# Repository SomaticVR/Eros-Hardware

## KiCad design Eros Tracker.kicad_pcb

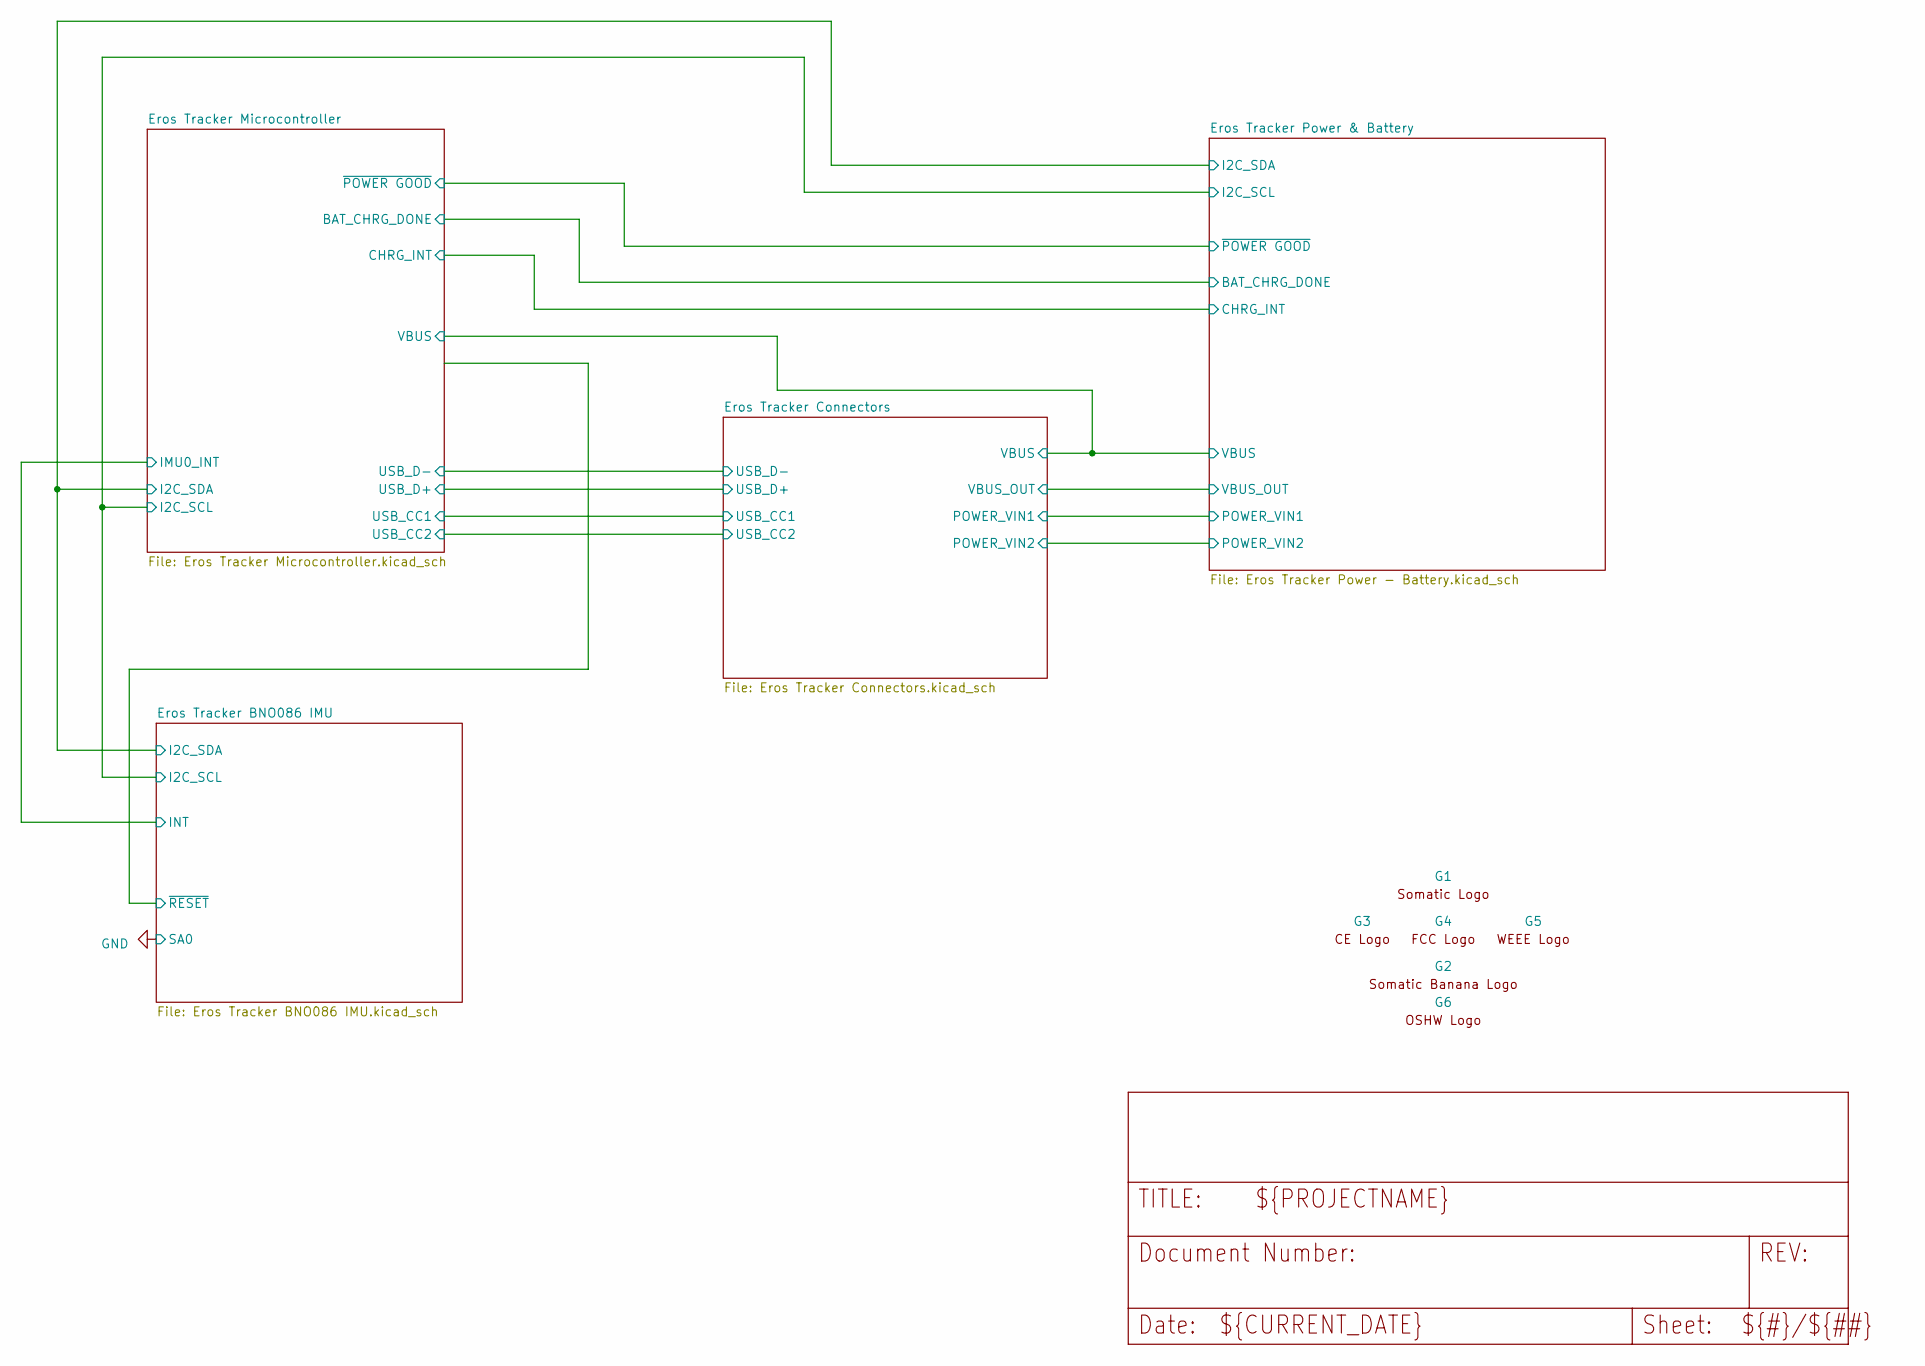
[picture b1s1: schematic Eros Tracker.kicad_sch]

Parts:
G1: SomaticLogo
G2: SomaticBananaLogo
G3: CE-Logo_7.0x5.0mm_SilkScreen
G4: FCC-Logo_6.2x5.0mm_SilkScreen
G5: WEEE-Logo_4.2x6mm_SilkScreen
G6: OSHW-Logo2_7.3x6mm_SilkScreen

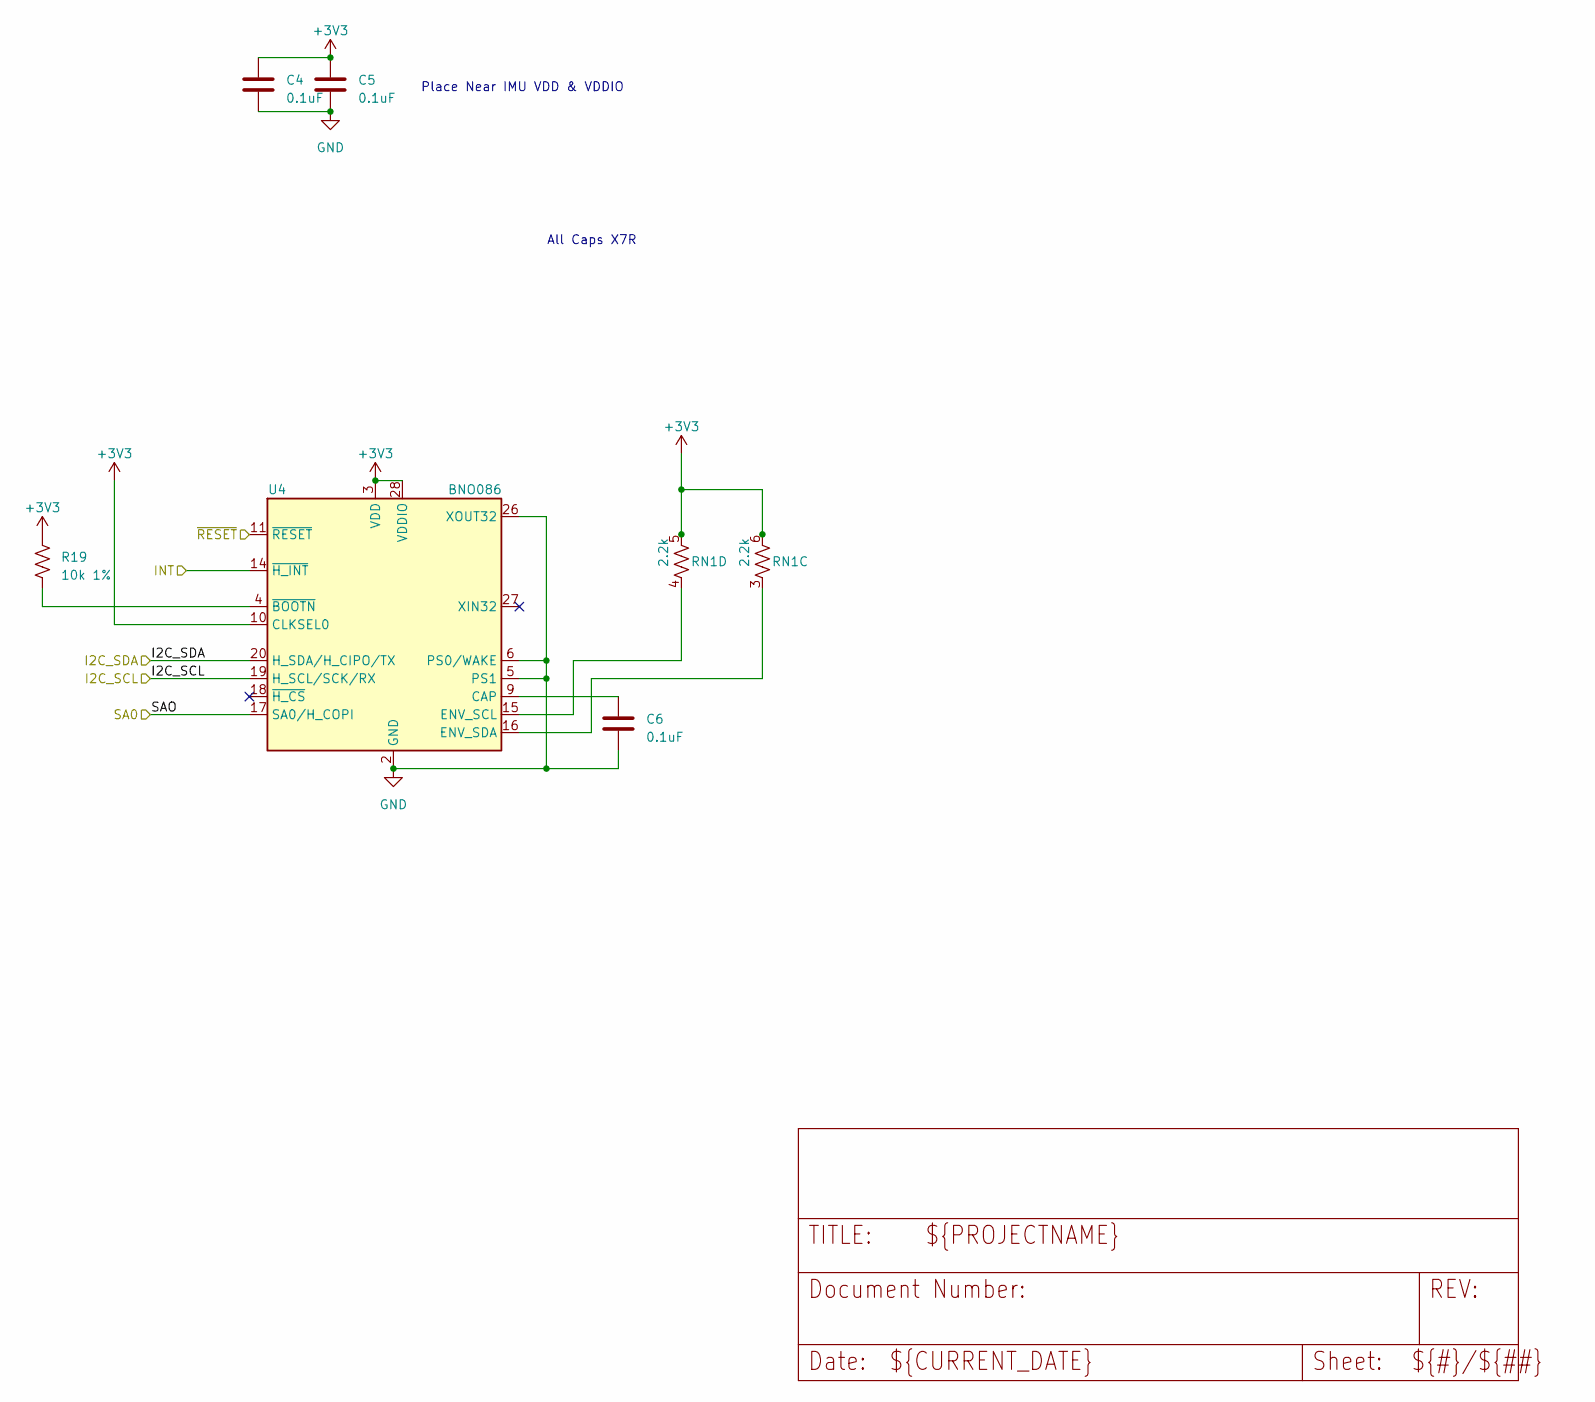
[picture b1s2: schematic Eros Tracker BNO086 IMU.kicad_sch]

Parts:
C4, C5, C6: 0.1uF; C_0402_1005Metric; Manufacturer_Part_Number CL05B104KA5NNNC; Mouser Part Number 187-CL05B104KA5NNNC
R19: 10k 1%; R_0402_1005Metric; Manufacturer_Part_Number RT0402FRE0710KL; Mouser Part Number 603-RT0402FRE0710KL
RN1: 2.2k; CAY10-xxxJ4; Manufacturer_Part_Number CAY10-222J4LF; Mouser Part Number 652-CAY10-222J4LF
U4: BNO086; LGA-28_5.2x3.8mm_P0.5mm; Manufacturer_Part_Number BNO086; DigiKey Part Number 1888-BNO086CT-ND

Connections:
+3V3: C4.1, C5.1, R19.1, RN1.5, RN1.6, U4.3 (VDD), U4.10 (CLKSEL0), U4.28 (VDDIO); also elsewhere on the board
/Eros Tracker BNO086 IMU/I2C_SCL: U4.19 (H_SCL/SCK/RX); also elsewhere on the board
/Eros Tracker BNO086 IMU/I2C_SDA: U4.20 (H_SDA/H_CIPO/TX); also elsewhere on the board
/Eros Tracker BNO086 IMU/INT: U4.14 (~H_INT); also elsewhere on the board
/Eros Tracker BNO086 IMU/~RESET: U4.11 (~RESET)
GND: C4.2, C5.2, C6.2, U4.2 (GND), U4.5 (PS1), U4.6 (PS0/WAKE), U4.17 (SA0/H_COPI), U4.25 (GNDIO), U4.26 (XOUT32); also elsewhere on the board
unnamed: C6.1, U4.9 (CAP)
unnamed: RN1.4, U4.15 (ENV_SCL)
unnamed: RN1.3, U4.16 (ENV_SDA)
unnamed: R19.2, U4.4 (~BOOTN)

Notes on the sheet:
Place Near IMU VDD & VDDIO
All Caps X7R

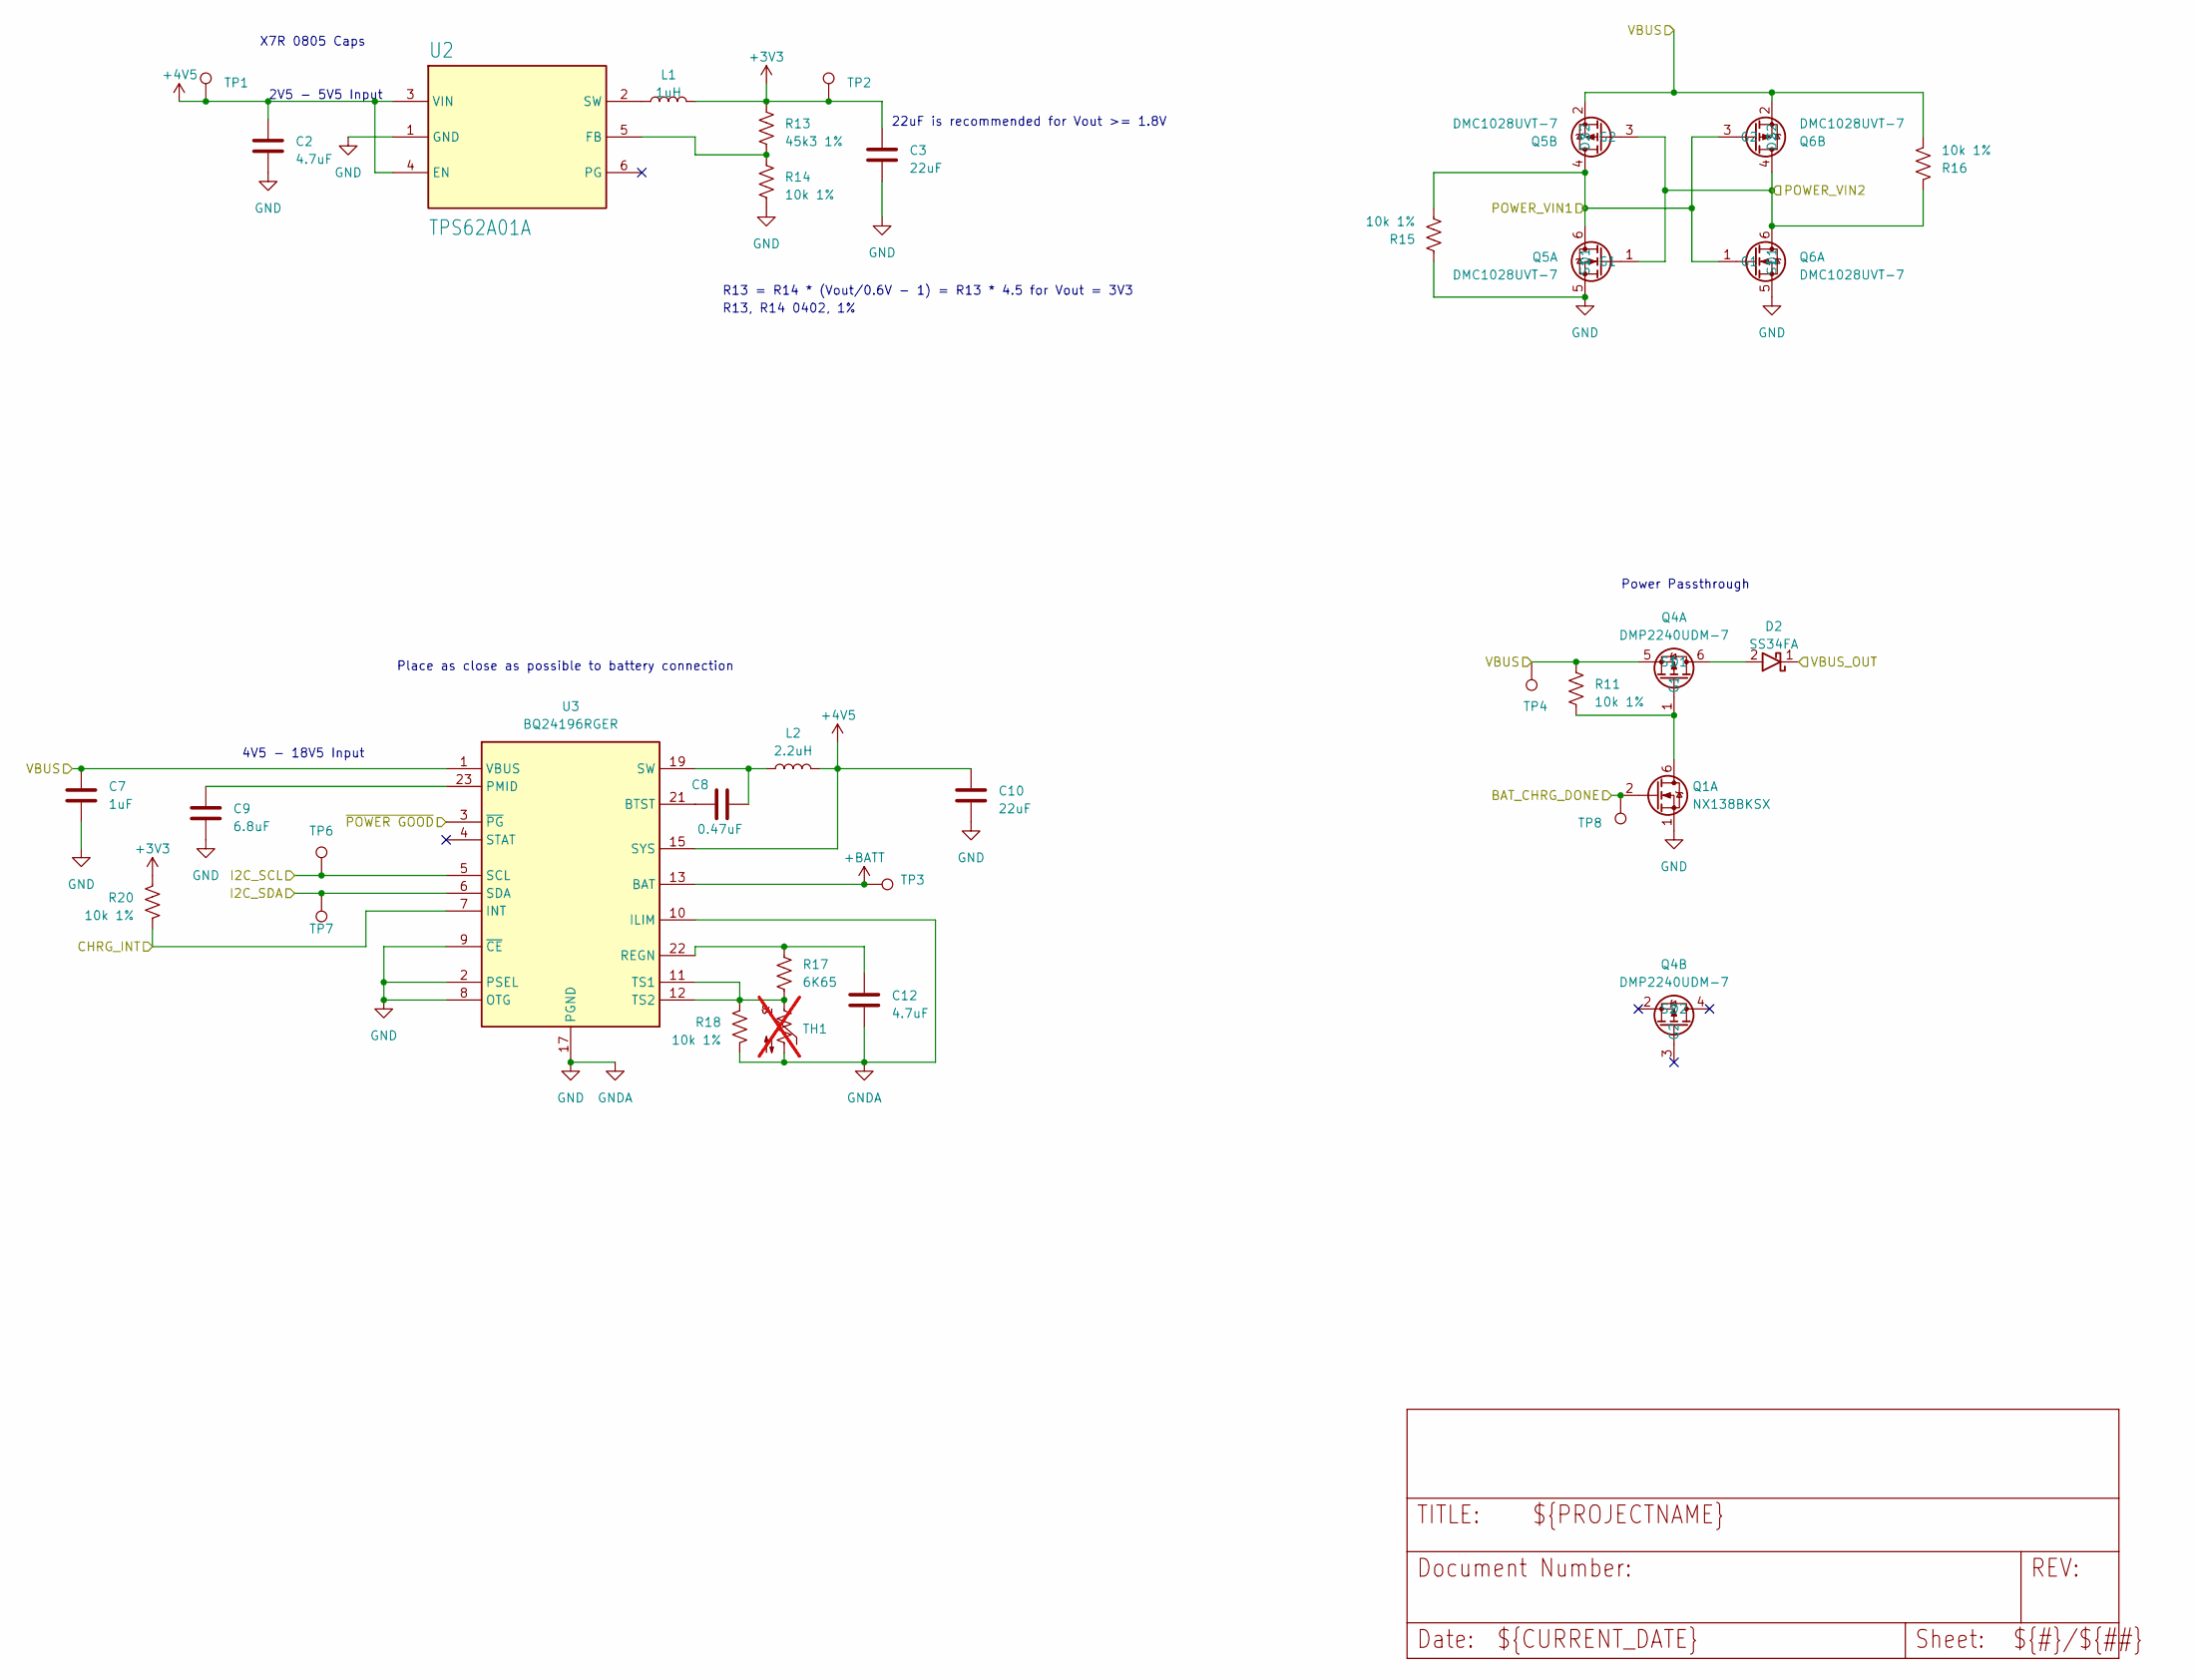
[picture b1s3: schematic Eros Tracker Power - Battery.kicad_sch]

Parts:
C2, C12: 4.7uF; C_0603_1608Metric; Manufacturer_Part_Number GRM188Z71C475KE21D; Mouser Part Number 81-GRM188Z71C475KE1D
C3, C10: 22uF; C_0805_2012Metric; Manufacturer_Part_Number GRM21BZ71A226ME15L; Mouser Part Number 81-GRM21BZ71A226ME5L
C7: 1uF; C_0603_1608Metric; Manufacturer_Part_Number MLASU168AB7105KTNA01; Mouser Part Number 963-MLASU168AB7105KT
C8: 0.47uF; C_0402_1005Metric; Manufacturer_Part_Number CC0402KRX7R6BB474; Mouser Part Number 603-CC0402KR6BB474
C9: 6.8uF; C_1210_3225Metric; Manufacturer_Part_Number C3225X7R1E685K250AB; Mouser Part Number 810-C3225X7R1E685K11
D2: SS34FA; SODFL3618X143N; Mouser Part Number 512-SS34FA
L1: 1uH; DFE2HCAH1R0MJ0L; Manufacturer_Part_Number DFE252012F-1R0M=P2; Mouser Part Number 81-DFE252012F-1R0MP2
L2: 2.2uH; 1277ASH100MP2; Manufacturer_Part_Number DFE322512F-2R2M=P2; Mouser Part Number 81-DFE322512F-2R2MP2
Q1: NX138BKSX; SOT65P210X110-6N; Mouser Part Number 771-NX138BKSX
Q4: DMP2240UDM-7; SOT95P285X140-6N; Mouser Part Number 621-DMP2240UDM-7
Q5, Q6: DMC1028UVT-7; SOT95P285X140-6N; Mouser Part Number 621-DMC1028UVT-7
R11, R14, R15, R16, R18, R20: 10k 1%; R_0402_1005Metric; Manufacturer_Part_Number RT0402FRE0710KL; Mouser Part Number 603-RT0402FRE0710KL
R13: 45k3 1%; R_0402_1005Metric; Manufacturer_Part_Number RR0510P-4532-D; Mouser Part Number 754-RR0510P-4532D
R17: 6K65; R_0402_1005Metric; Manufacturer_Part_Number RT0402DRE076K65L; Mouser Part Number 603-RT0402DRE076K65L
TH1: 10k; R_0402_1005Metric; Manufacturer_Part_Number NTCG103UH103HT1; Mouser Part Number 810-NTCG103UH103HT1; not fitted
TP1, TP2, TP3, TP4, TP6, TP7, TP8: TestPoint; TestPoint_Pad_D1.0mm
U2: TPS62A01A; TPS62A0xA-SOT-563; Manufacturer_Part_Number TPS62A01ADRLR; Mouser Part Number 595-TPS62A01ADRLR
U3: BQ24196RGER; QFN50P400X400X100-25N-D; Mouser Part Number 595-BQ24196RGER

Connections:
+3V3: C3.1, L1.2, R13.1, R20.1, TP2.1; also elsewhere on the board
+4V5: C2.1, C10.1, L2.2, TP1.1, U2.3 (VIN), U2.4 (EN), U3.15 (SYS), U3.16 (SYS_2); also elsewhere on the board
+BATT: TP3.1, U3.13 (BAT), U3.14 (BAT_2); also elsewhere on the board
/Eros Tracker BNO086 IMU/I2C_SCL: TP6.1, U3.5 (SCL); also elsewhere on the board
/Eros Tracker BNO086 IMU/I2C_SDA: TP7.1, U3.6 (SDA); also elsewhere on the board
/Eros Tracker Connectors/POWER_VIN1: Q5.4 (D2), Q5.6 (D1), Q6.1 (G1), Q6.3 (G2), R15.2; also elsewhere on the board
/Eros Tracker Connectors/POWER_VIN2: Q5.1 (G1), Q5.3 (G2), Q6.4 (D2), Q6.6 (D1), R16.1; also elsewhere on the board
/Eros Tracker Connectors/VBUS: C7.1, Q4.5 (S1), Q5.2 (S2), Q6.2 (S2), R11.1, R16.2, TP4.1, U3.1 (VBUS), U3.24 (VBUS_2); also elsewhere on the board
/Eros Tracker Connectors/VBUS_OUT: D2.1 (K); also elsewhere on the board
/Eros Tracker Microcontroller/BAT_CHRG_DONE: Q1.2 (G1), TP8.1; also elsewhere on the board
/Eros Tracker Microcontroller/CHRG_INT: R20.2, U3.7 (INT); also elsewhere on the board
/Eros Tracker Microcontroller/~POWER GOOD: U3.3 (~PG); also elsewhere on the board
GND: C2.2, C3.2, C7.2, C9.2, C10.2, C12.2, Q1.1 (S1), Q5.5 (S1), Q6.5 (S1), R14.2, R15.1, R18.2, TH1.2, U2.1 (GND), U3.2 (PSEL), U3.8 (OTG), U3.9 (~CE), U3.10 (ILIM), U3.17 (PGND), U3.18 (PGND_2), U3.25 (EP); also elsewhere on the board
unnamed: D2.2 (A), Q4.6 (D1)
unnamed: Q1.6 (D1), Q4.1 (G1), R11.2
unnamed: R13.2, R14.1, U2.5 (FB)
unnamed: L1.1, U2.2 (SW)
unnamed: C8.1, U3.21 (BTST)
unnamed: C9.1, U3.23 (PMID)
unnamed: C12.1, R17.1, U3.22 (REGN)
unnamed: C8.2, L2.1, U3.19 (SW), U3.20 (SW_2)
unnamed: R17.2, R18.1, TH1.1, U3.11 (TS1), U3.12 (TS2)

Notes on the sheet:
22uF is recommended for Vout >= 1.8V
R13 = R14 * (Vout/0.6V - 1) = R13 * 4.5 for Vout = 3V3
Power Passthrough
2V5 - 5V5 Input
4V5 - 18V5 Input
X7R 0805 Caps
Place as close as possible to battery connection
R13, R14 0402, 1%

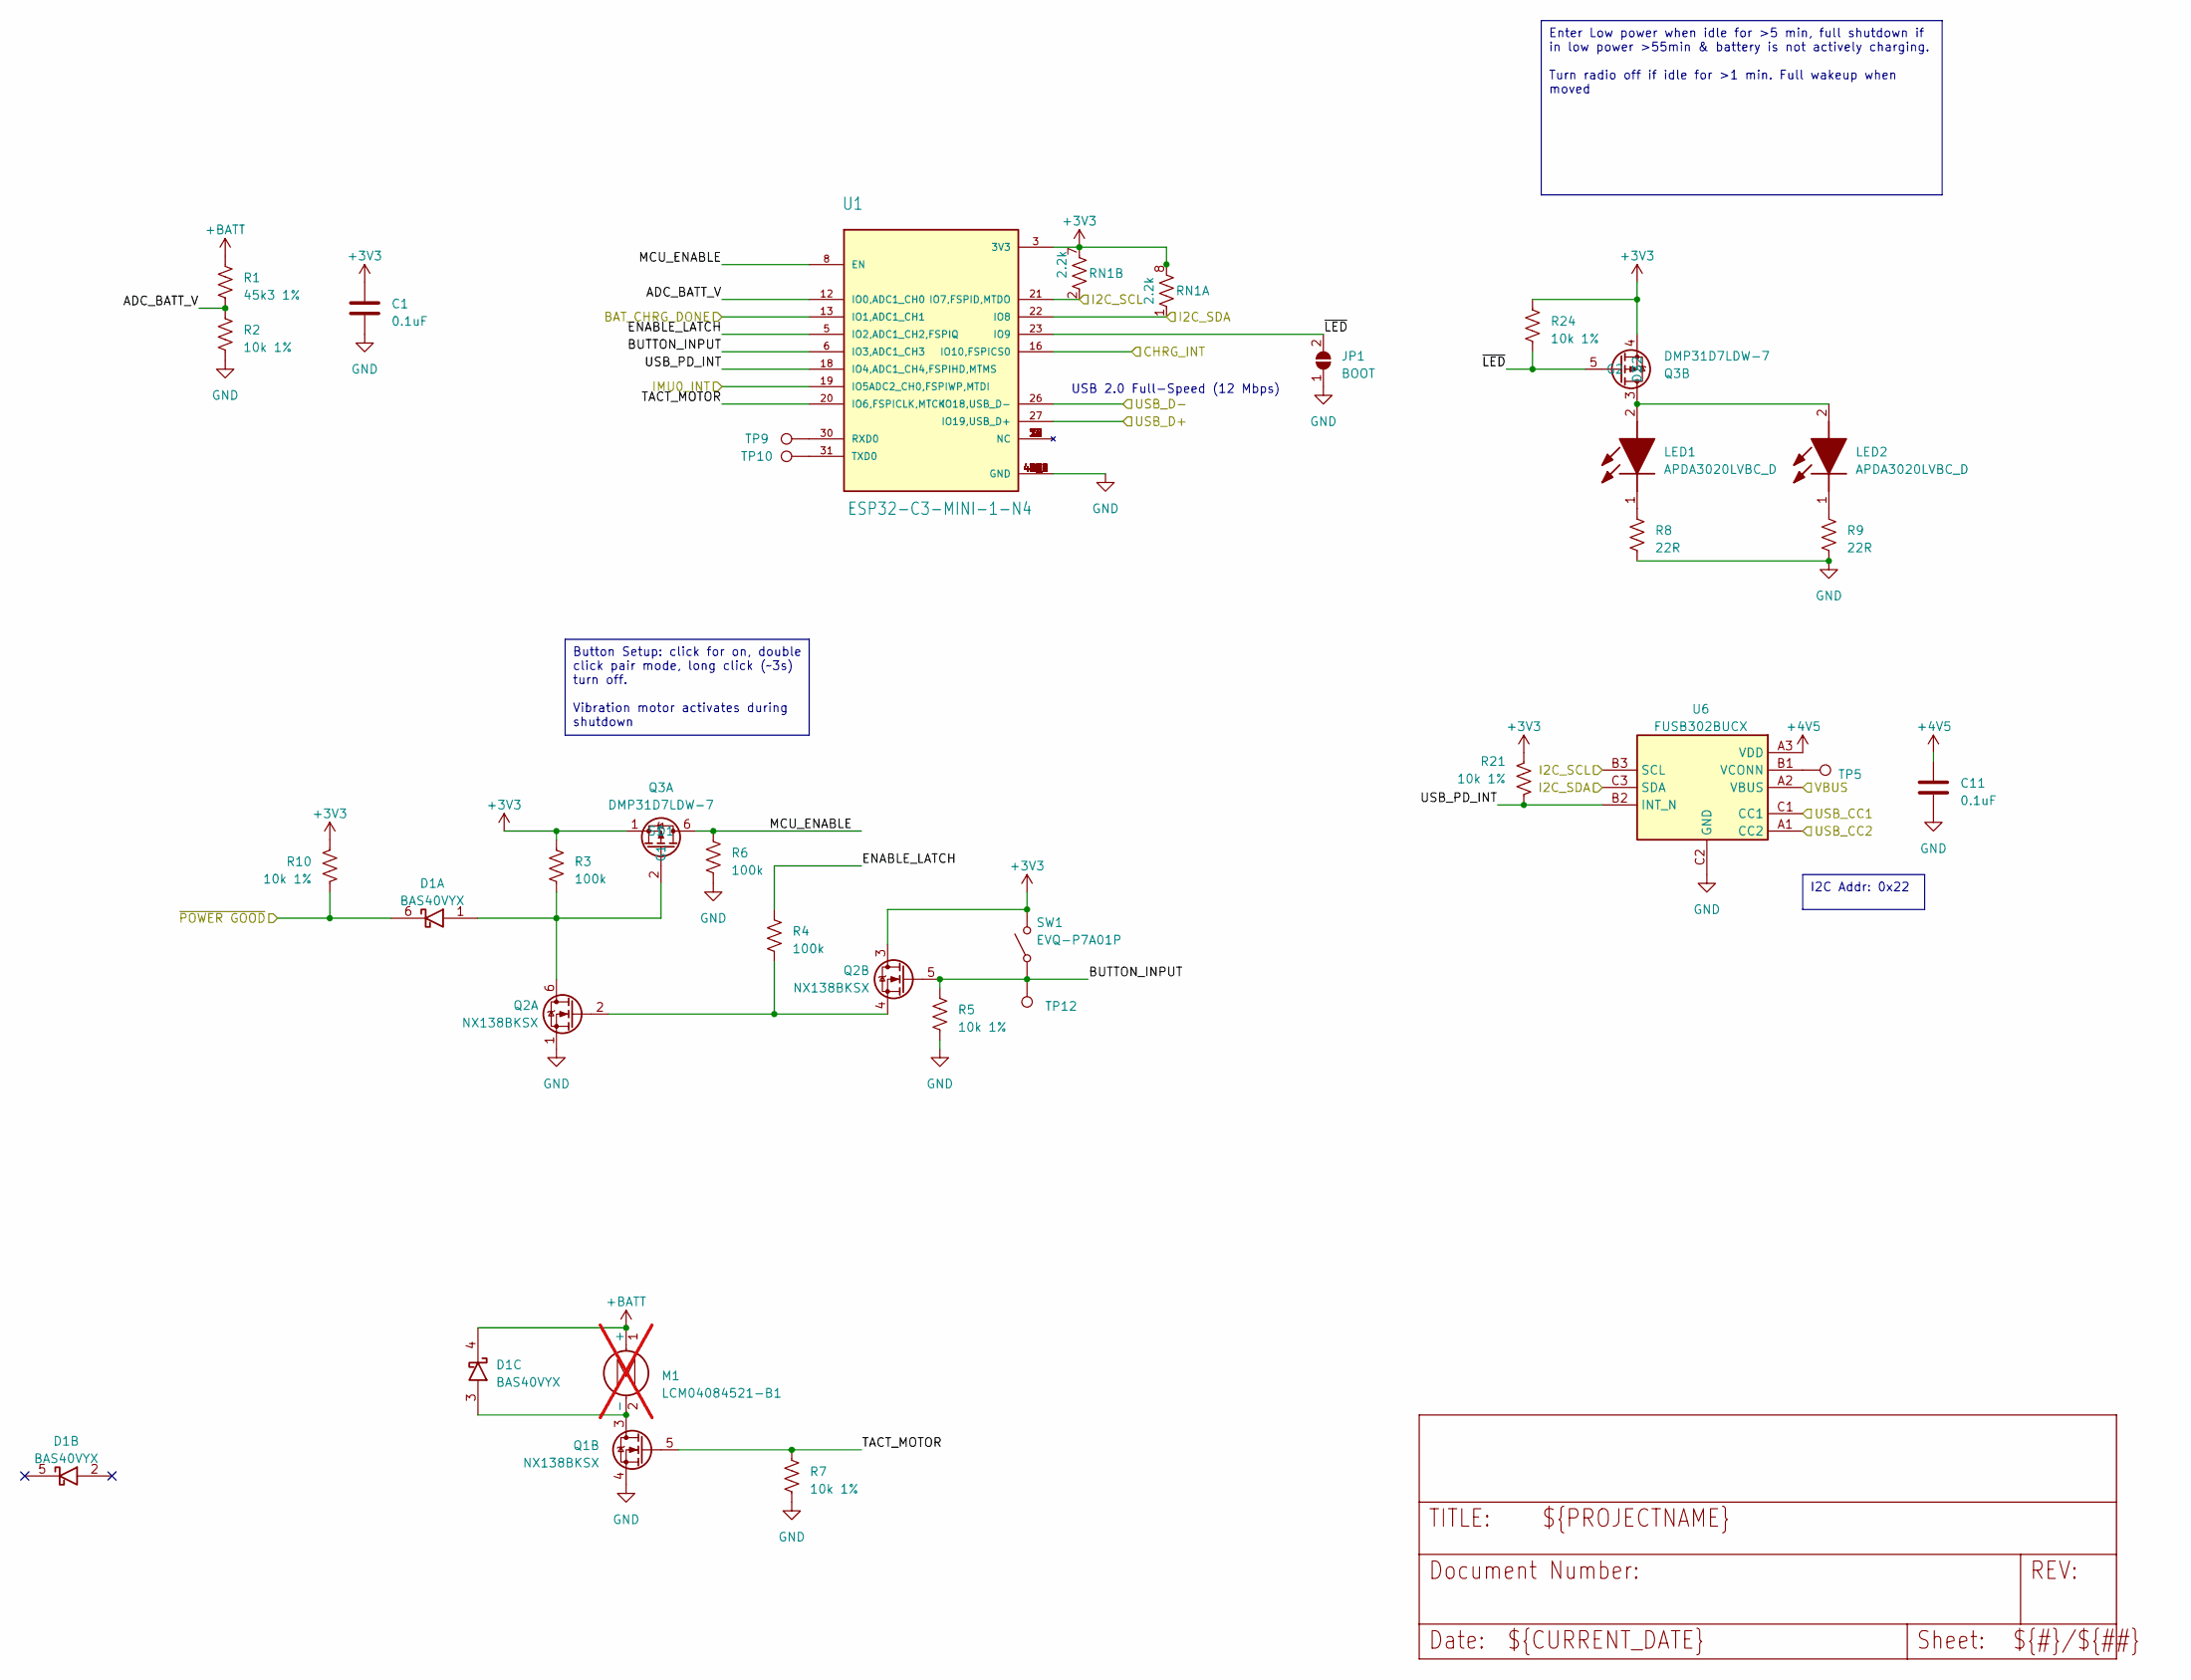
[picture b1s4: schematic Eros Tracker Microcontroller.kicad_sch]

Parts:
C1, C11: 0.1uF; C_0402_1005Metric; Manufacturer_Part_Number CL05B104KA5NNNC; Mouser Part Number 187-CL05B104KA5NNNC
D1: BAS40VYX; SOT65P210X110-6N; Manufacturer_Part_Number BAS40VYX
JP1: BOOT; SolderJumper-2_P1.3mm_Open_RoundedPad1.0x1.5mm
LED1, LED2: APDA3020LVBC_D; APDA3020LVBCD; Mouser Part Number 604-APDA3020LVBCD
M1: LCM04084521-B1; not fitted
Q1, Q2: NX138BKSX; SOT65P210X110-6N; Mouser Part Number 771-NX138BKSX
Q3: DMP31D7LDW-7; SOT65P210X110-6N; Mouser Part Number 621-DMP31D7LDW-7
R1: 45k3 1%; R_0402_1005Metric; Manufacturer_Part_Number RR0510P-4532-D; Mouser Part Number 754-RR0510P-4532D
R2, R5, R7, R10, R21, R24: 10k 1%; R_0402_1005Metric; Manufacturer_Part_Number RT0402FRE0710KL; Mouser Part Number 603-RT0402FRE0710KL
R3, R4, R6: 100k; R_0402_1005Metric; Manufacturer_Part_Number RT0402FRE07100KL; Mouser Part Number 603-RT0402FRE07100KL
R8, R9: 22R; R_0402_1005Metric; Manufacturer_Part_Number RT0402FRE0722RL; Mouser Part Number 603-RT0402FRE0722RL
RN1: 2.2k; CAY10-xxxJ4; Manufacturer_Part_Number CAY10-222J4LF; Mouser Part Number 652-CAY10-222J4LF
SW1: EVQ-P7A01P; EVQ-P7J01P; Mouser Part Number 667-EVQP7A01P
TP5, TP9, TP10, TP12: TestPoint; TestPoint_Pad_D1.0mm
U1: ESP32-C3-MINI-1-N4; XCVR_ESP32-C3-MINI-1-N4; Manufacturer_Part_Number ESP32-C3-MINI-1-N4; Mouser Part Number 356-ESP32-C3-MINI1N4
U6: FUSB302BUCX; BGA9C40P3X3_122X126X53; Mouser Part Number 512-FUSB302BUCX

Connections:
+3V3: C1.1, Q2.3 (D2), Q3.1 (S1), Q3.4 (S2), R3.1, R10.1, R21.1, R24.1, RN1.7, RN1.8, SW1.3 (COM_2), SW1.4 (COM_1), U1.3 (3V3); also elsewhere on the board
+4V5: C11.1, U6.A3 (VDD); also elsewhere on the board
+BATT: D1.4 (K3), M1.1 (+), R1.1; also elsewhere on the board
/Eros Tracker BNO086 IMU/I2C_SCL: RN1.2, U1.21 (IO7,FSPID,MTDO), U6.B3 (SCL); also elsewhere on the board
/Eros Tracker BNO086 IMU/I2C_SDA: RN1.1, U1.22 (IO8), U6.C3 (SDA); also elsewhere on the board
/Eros Tracker BNO086 IMU/INT: U1.19 (IO5ADC2_CH0,FSPIWP,MTDI); also elsewhere on the board
/Eros Tracker Connectors/USB_CC1: U6.C1 (CC1); also elsewhere on the board
/Eros Tracker Connectors/USB_CC2: U6.A1 (CC2); also elsewhere on the board
/Eros Tracker Connectors/USB_D+: U1.27 (IO19,USB_D+); also elsewhere on the board
/Eros Tracker Connectors/USB_D-: U1.26 (IO18,USB_D-); also elsewhere on the board
/Eros Tracker Connectors/VBUS: U6.A2 (VBUS); also elsewhere on the board
/Eros Tracker Microcontroller/ADC_BATT_V: R1.2, R2.1, U1.12 (IO0,ADC1_CH0)
/Eros Tracker Microcontroller/BAT_CHRG_DONE: U1.13 (IO1,ADC1_CH1); also elsewhere on the board
/Eros Tracker Microcontroller/BUTTON_INPUT: Q2.5 (G2), R5.1, SW1.1 (NO_1), SW1.2 (NO_2), TP12.1, U1.6 (IO3,ADC1_CH3)
/Eros Tracker Microcontroller/CHRG_INT: U1.16 (IO10,FSPICS0); also elsewhere on the board
/Eros Tracker Microcontroller/ENABLE_LATCH: R4.1, U1.5 (IO2,ADC1_CH2,FSPIQ)
/Eros Tracker Microcontroller/MCU_ENABLE: Q3.6 (D1), R6.1, U1.8 (EN)
/Eros Tracker Microcontroller/TACT_MOTOR: Q1.5 (G2), R7.1, U1.20 (IO6,FSPICLK,MTCK)
/Eros Tracker Microcontroller/USB_PD_INT: R21.2, U1.18 (IO4,ADC1_CH4,FSPIHD,MTMS), U6.B2 (INT_N)
/Eros Tracker Microcontroller/~LED: JP1.2 (B), Q3.5 (G2), R24.2, U1.23 (IO9)
/Eros Tracker Microcontroller/~POWER GOOD: D1.6 (K1), R10.2; also elsewhere on the board
GND: C1.2, C11.2, JP1.1 (A), Q1.4 (S2), Q2.1 (S1), R2.2, R5.2, R6.2, R7.2, R8.2, R9.2, U1.1 (GND), U1.2 (GND), U1.11 (GND), U1.14 (GND), U1.36 (GND), U1.37 (GND), U1.38 (GND), U1.39 (GND), U1.40 (GND), U1.41 (GND), U1.42 (GND), U1.43 (GND), U1.44 (GND), U1.45 (GND), U1.46 (GND), U1.47 (GND), U1.48 (GND), U1.49_1 (GND), U1.49_2 (GND), U1.49_3 (GND), U1.49_4 (GND), U1.49_5 (GND), U1.49_6 (GND), U1.49_7 (GND), U1.49_8 (GND), U1.49_9 (GND), U1.50 (GND), U1.51 (GND), U1.52 (GND), U1.53 (GND), U6.C2 (GND); also elsewhere on the board
unnamed: D1.1 (A1), Q2.6 (D1), Q3.2 (G1), R3.2
unnamed: D1.3 (A3), M1.2 (-), Q1.3 (D2)
unnamed: LED1.2 (A), LED2.2 (A), Q3.3 (D2)
unnamed: LED1.1 (K), R8.1
unnamed: LED2.1 (K), R9.1
unnamed: Q2.2 (G1), Q2.4 (S2), R4.2
unnamed: TP9.1, U1.30 (RXD0)
unnamed: TP10.1, U1.31 (TXD0)
unnamed: TP5.1, U6.B1 (VCONN)

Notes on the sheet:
Button Setup: click for on, double click pair mode, long click (~3s) turn off. Vibration motor activates during shutdown
Enter Low power when idle for >5 min, full shutdown if in low power >55min & battery is not actively charging. Turn radio off if idle for >1 min. Full wakeup when moved
I2C Addr: 0x22
USB 2.0 Full-Speed (12 Mbps)

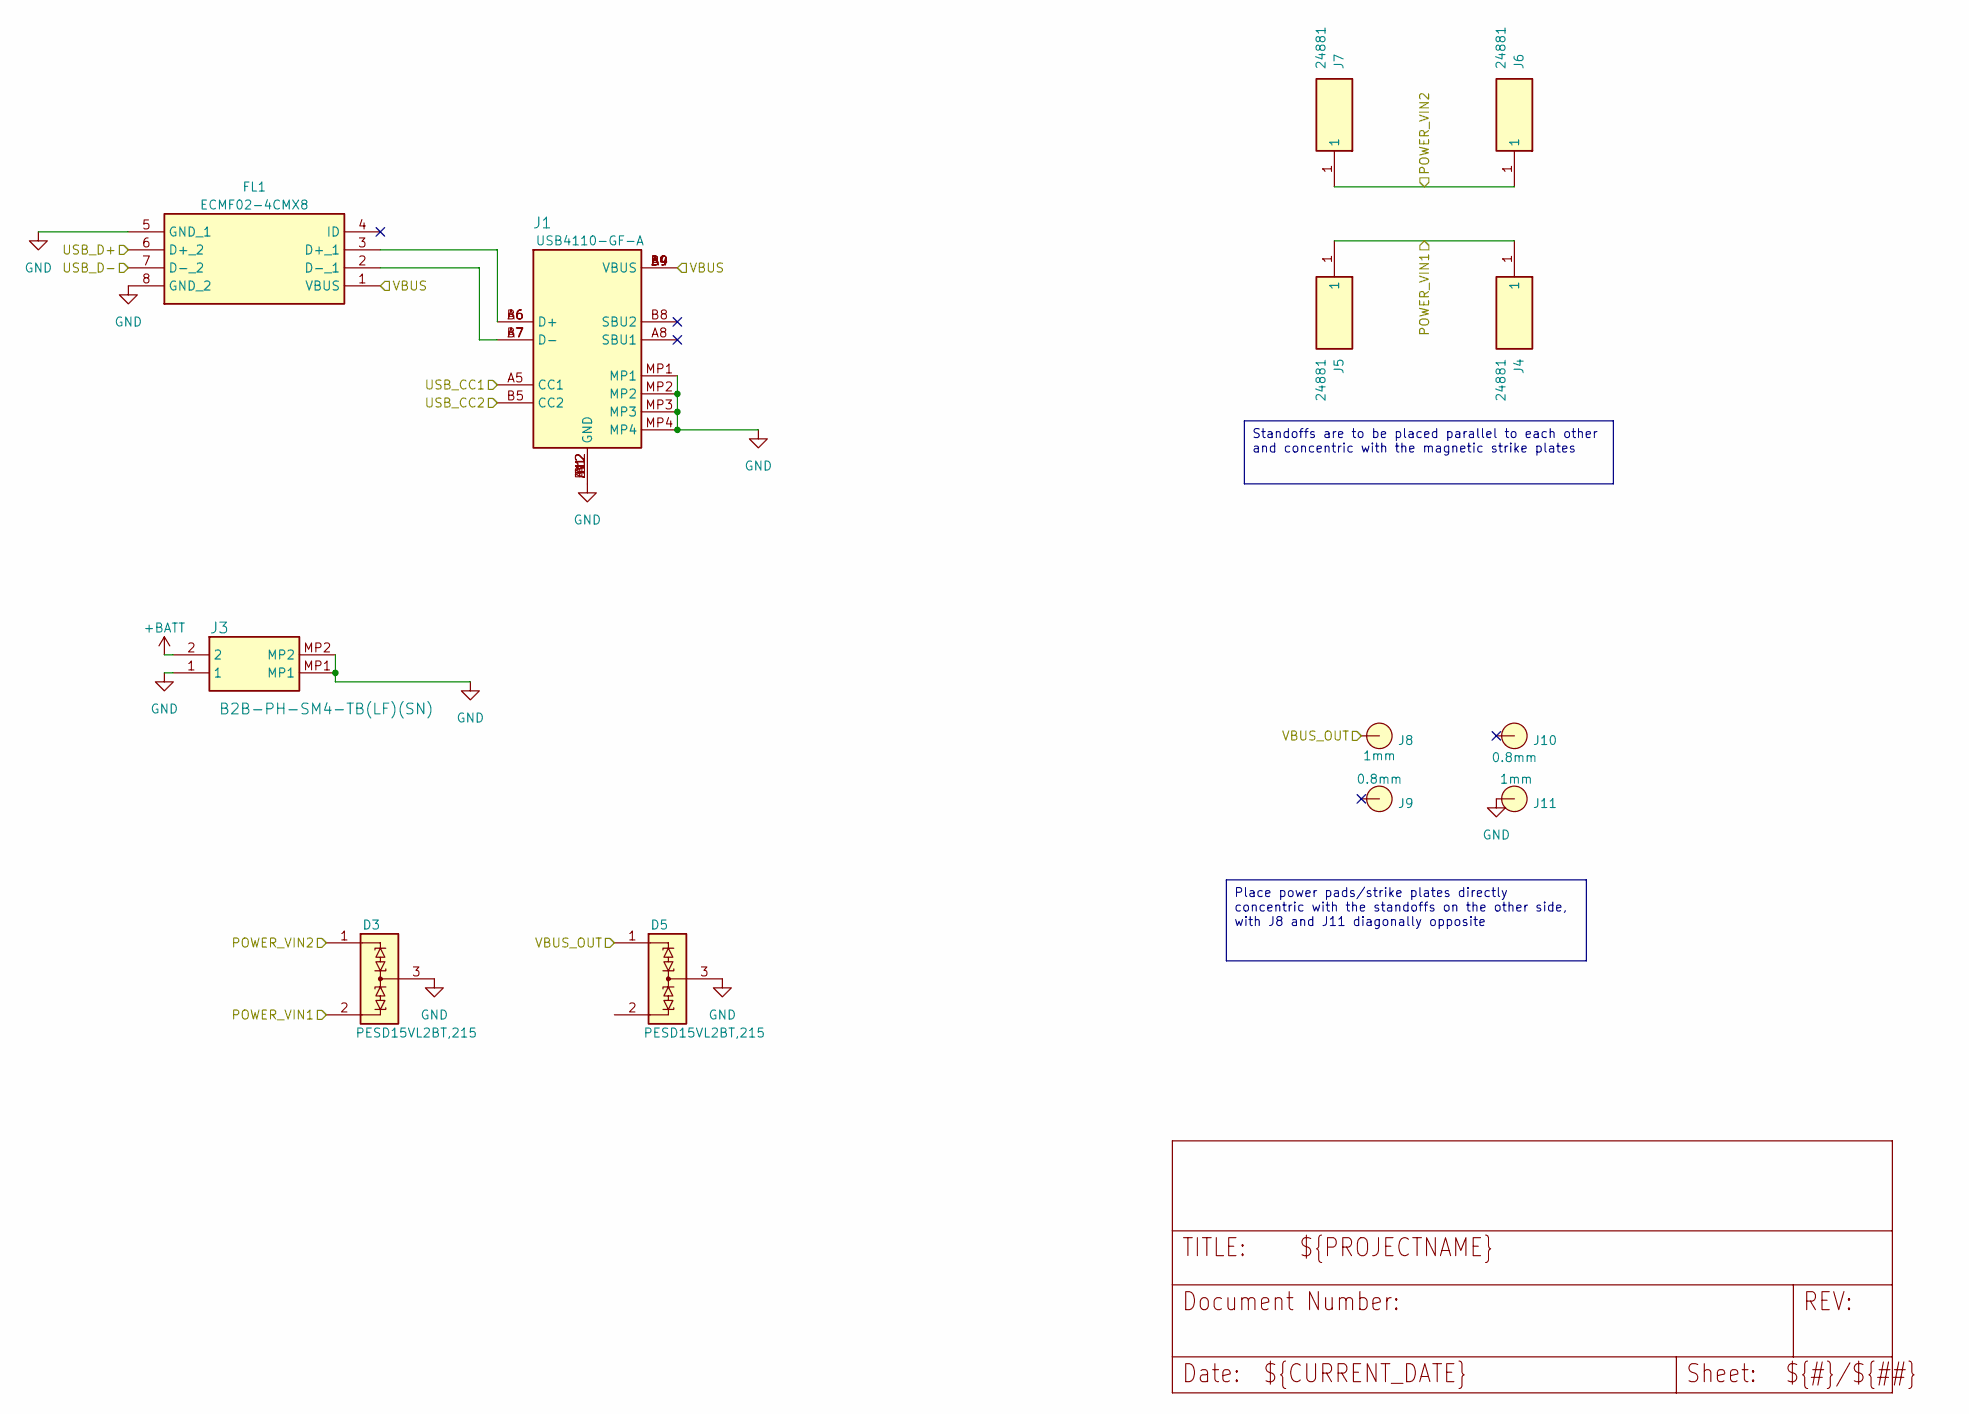
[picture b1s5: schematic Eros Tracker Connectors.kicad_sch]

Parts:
D3, D5: PESD15VL2BT,215; SOT95P230X110-3N; Mouser Part Number 771-PESD15VL2BT-T/R
FL1: ECMF02-4CMX8; ECMF024CMX8; Mouser Part Number 511-ECMF02-4CMX8
J1: USB4110-GF-A; USB4110GFA; Mouser Part Number 640-USB4110-GF-A
J3: B2B-PH-SM4-TB(LF)(SN); B2BPHSM4TBLFSN; Manufacturer_Part_Number B2B-PH-SM4-TB(LF)(SN); DigiKey Part Number 455-B2B-PH-SM4-TBCT-ND
J4, J5, J6, J7: 24881; 2488x-NPTH; Mouser Part Number 534-24881
J8, J11: 1mm; 10mmDisc
J9, J10: 0.8mm; 10mmDisc

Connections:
+BATT: J3.2; also elsewhere on the board
/Eros Tracker Connectors/POWER_VIN1: D3.2, J4.1, J5.1; also elsewhere on the board
/Eros Tracker Connectors/POWER_VIN2: D3.1, J6.1, J7.1; also elsewhere on the board
/Eros Tracker Connectors/USB_CC1: J1.A5 (CC1); also elsewhere on the board
/Eros Tracker Connectors/USB_CC2: J1.B5 (CC2); also elsewhere on the board
/Eros Tracker Connectors/USB_D+: FL1.6 (D+_2); also elsewhere on the board
/Eros Tracker Connectors/USB_D-: FL1.7 (D-_2); also elsewhere on the board
/Eros Tracker Connectors/VBUS: FL1.1 (VBUS), FL1.10, J1.A4 (VBUS), J1.A9 (VBUS), J1.B4 (VBUS), J1.B9 (VBUS); also elsewhere on the board
/Eros Tracker Connectors/VBUS_OUT: D5.1, J8.1; also elsewhere on the board
GND: D3.3, D5.3, FL1.5 (GND_1), FL1.8 (GND_2), FL1.9, FL1.12, J1.A1 (GND), J1.A12 (GND), J1.B1 (GND), J1.B12 (GND), J1.MP1, J1.MP2, J1.MP3, J1.MP4, J3.1, J3.MP1, J3.MP2, J11.1; also elsewhere on the board
unnamed: FL1.3 (D+_1), J1.A6 (D+), J1.B6 (D+)
unnamed: FL1.2 (D-_1), J1.A7 (D-), J1.B7 (D-)

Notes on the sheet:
Standoffs are to be placed parallel to each other and concentric with the magnetic strike plates
Place power pads/strike plates directly concentric with the standoffs on the other side, with J8 and J11 diagonally opposite

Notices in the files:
parts and their libraries:
Copyright 2021 Accelerated Designs. All rights reserved.
